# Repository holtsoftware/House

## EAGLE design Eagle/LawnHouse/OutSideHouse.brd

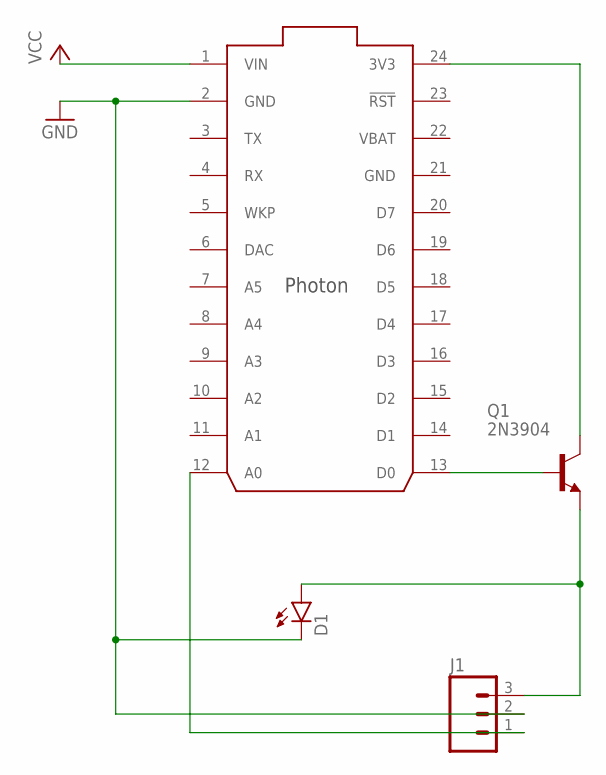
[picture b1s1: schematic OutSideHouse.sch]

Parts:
D1: LED5MM
J1: M03LONGPADS; 1X03_LONGPADS
Q1: 2N3904; TO92
U$1: PHOTON_WITH_HEADERS; PHOTON

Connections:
GND: D1.K (C), J1.2, U$1.2 (GND), U$1.21 (GND)
unnamed: Q1.1 (C), U$1.24 (3V3)
unnamed: Q1.2 (B), U$1.13 (D0)
unnamed: D1.A, J1.3, Q1.3 (E)
unnamed: J1.1, U$1.12 (A0)
VBAT: U$1.22 (VBAT)
VCC: U$1.1 (VIN)

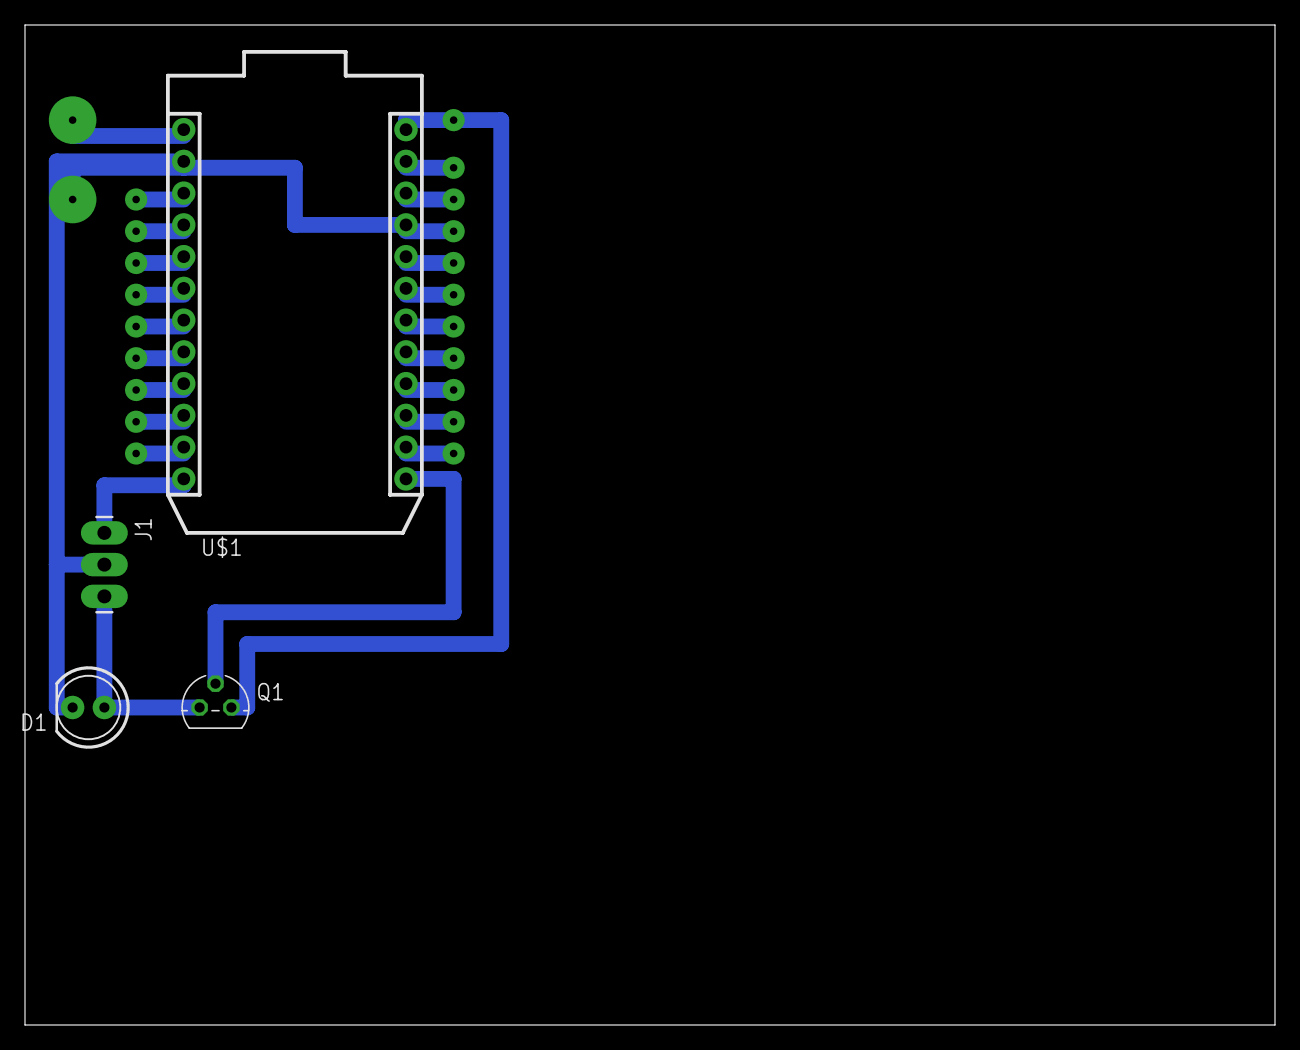
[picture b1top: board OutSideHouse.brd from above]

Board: 2 copper layers, 100.0 x 80.0 mm, 4 parts (0 on the bottom side), 5 nets.

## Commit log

2013-11-29 Inital Checkin.
2013-12-12 Have Room adding working.
2013-12-12 Added missing files.
2014-01-24 Added Inital Comps and Color source.
2014-01-24 Added 768 comp.
2014-04-26 commit before rebuild.
2014-04-26 Removed.
2016-04-03 Deleted Old Stuff
2016-04-04 Added new app for RaspberryPi Controller
2016-04-05 Updated project to use Caliburnmicro instead of MVVMLight
2016-04-06 Filled out CurrentWeather
2016-04-12 Added local Icons from Underground Weather. Converted Weather into its own View/ViewModel
2016-04-20 Started adding BME280 reader
2016-04-21 added tempratue
2016-04-25 getting server up and working
2016-05-02 Removed References to http server
2016-05-09 Progress
2016-05-11 Fixed calculation of humidity
2016-05-31 Added Module for Screen Driver
2016-05-31 Added PiHolder
2016-06-05 Added Object
2016-06-05 Some updates
2016-06-05 updated size
2016-06-05 updated placements
2016-06-05 Updated Sizes
2016-06-08 Updated some scad files
2016-06-15 Added some files.
2016-06-19 Restart
2016-06-29 Updated eagle file. Added .NET Core Web app.
2016-07-02 Added some projects including the test project.
2016-07-02 Got more items setup.
2016-07-03 Added the migration to the database project. Added the controller for devices. Tests work for controller as well.
2016-07-04 Added some items from the sample project to get identity up and running faster.
2016-07-04 Finished building out and testing Devices controller
2016-07-05 Added Name to ApplicationUser.
2016-07-12 Updated How Devices are handled
2016-07-13 Added JsonProperty to Devices so that they have the case to match the ts script. Updated script to the TS instead of the javascript.
2016-07-14 Got adding device working again on the client side.
2016-07-14 Got editing working
2016-07-14 Added IsReadOnly to prevent editing of some devices. Updated Startup so the url the site runs on can be changed.
2016-07-15 Added Thermostat project
2016-07-15 Changes to all projet to be deployed to the pi.
2016-07-19 configuring a bunch of stuff
2016-07-20 Added the timer service. Implemented time updating on Shell View.
2016-07-26 Changed HttpClients and got was able to retreave the authz cookie after login.
2016-07-27 Added test for ServerDataContext
2016-07-27 Added Get Devices Test
2016-07-28 Added Business project. Added Home View. updated boot to pull devices from server. added sync service.
2016-07-29 Updates.
2016-08-01 Added TemperatureDefaults
2016-08-02 Added Logging backgroundTask
2016-08-02 Upgraded projects to target aniversary update.
2016-08-03 Updating TemperatureSetting Object to support database and add time object as well removed month.
2016-08-03 Started building up the get test for TemperatureSettings
2016-08-04 Added Controller app that will be the main ui app on the pi.
2016-08-04 Added Client project
2016-08-09 Added ILoginViewModel
2016-08-09 Added NavigatedTo and NavigatedFrom to base viewmodel. Added Base View to provide NavigatedTo and NavigatedFrom functionality.
2016-08-10 Added ErrorViewModel to handel errors.
2016-08-10 Switched Dependency Injection to Unity Started Implementing Login to the server.
2016-08-10 Added Method to get list of roles from server for client apps. Added Tests for login to the server and getting a list of roles from the server.
2016-08-13 Got Login working for the UWP app. Updated the Android app to almost be in the same spot.
2016-08-15 More prograss on the android app.
2016-08-16 Changes for the Android app.
2016-08-17 Adding Menu and User. As well as started to build temperature setting view.
2016-08-17 Started Building out Temperature Setting page
2016-08-17 Default Temperature settings can be changed and saved now.
2016-08-18 Updates to TemperatureSettings
2016-08-18 Changing how the TemperatureSettings View looks
2016-08-18 Got the Day Defaults saving back to the database when the flyout closes. Started building out calander.
2016-08-19 Got Temperature week calander looking better
2016-08-19 Updates to get Time on dayofweek to work.
2016-08-22 Added TemperatureSection
2016-08-22 Got the page pulling in day time settings.
2016-08-22 Updateing what shows up in dropdown.
2016-08-24 Updated TemperatureEditing for times in a day.
2016-08-24 Got temperature setting entry control working the way i want it.
2016-08-25 Moving Boxes
2016-08-25 Start time is now relyable being filled in.
2016-08-25 Got StartTime and EndTime working reliably on the ui. added ability to delete temperature setting.
2016-08-26 Started Creating Logging AppService for Pi
2016-08-26 Building out Logging AppService
2016-08-27 Started adding LoggingSDK
2016-08-31 Added Server SDK. Building out Thermastat AppService.
2016-09-01 Added ability for to get configuration from thermostat.
2016-09-02 Removed Unused classes. Made it so Mock and tests projects compile again
2016-09-03 Added Common project with SimpleContainer and Extensions
2016-09-03 Added Ability to Post Entries into the database
2016-09-06 Updated how login works in ServerSDK. Added a way to post TemeratureEntries to the server.
2016-09-06 Added reference to the SimpleContainer so it can be passed into object Constructors
2016-09-06 Fixed Spelling issue
2016-09-06 Updates to Thermostat project
2016-09-06 Added PropertyChangedBase. Changed InitalMigration and removed FixedSpellingError migration. Created interface to interact with the background task on LocalTest
2016-09-09 moving computers
2016-09-10 Started Adding AutoGeneration Code
2016-09-12 Progress on the Generator
2016-09-13 Progress on Generator
2016-09-17 Updated to .net core 1.0.1
2016-10-01 Moving machines
2016-10-03 Building out the Generator
2016-10-05 More work on Generations
2016-10-18 Fixed some issues with generator. Added Example test for GetTemperatureEntryAsyncTest.
2016-10-18 Started created generation method for tests for server sdk.
2016-10-19 Progress on adding server sdk tests.
2016-10-20 Refectered how status are in the server sdk layor so there is only one enum needed.
2016-10-24 Progress on Generator. Updated how status is done.
2016-10-26 Progress on Test Generator
2016-10-29 Progress on ServerSDKTEst Generator
2016-11-04 Work on Generator
2016-11-10 Get Test finished first past implementation.
2016-11-10 Updated DataType.
2016-11-10 Fixed Issues with Generator
2016-11-10 Added Portable Project and updated Some code to cross between the Universal and Portable libraries
2016-11-21 Upgraded to .net core 1.1 and to visual studio 2017
2016-11-24 Upgraded to .net core 1.1 and visual studio 2017 RC
2016-11-28 Restructuring Generator and experimenting with docker.
2016-11-29 Started messing with CombinedGenerator
2016-11-30 fixed Build on Surface
2016-12-01 Got Task wrappers working for method declaration.
2016-12-11 Progress on Generator For ServerSDK

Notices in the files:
parts and their libraries:
SparkFun-LED: Licensing: Creative Commons ShareAlike 4.0 International - https://creativecommons.org/licenses/by-sa/4.0
